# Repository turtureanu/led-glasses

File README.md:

# led-glasses

Simple LED glasses controlled using a XIAO ESP32-S3 microcontroller.

## Credits

XIAO ESP32S3 footprint (XIAO-ESP32S3-SMD.kicad_mod): https://github.com/Seeed-Studio/OPL_Kicad_Library
XIAO ESP32S3 3D model: https://wiki.seeedstudio.com/xiao_esp32s3_getting_started/

Other 3D models sourced from EasyEDA.

## Todo

[-] Add battery switch circuit
[-] switch from 5V to 3V3, because 5V doesn't work with a battery
// breakout pins can be used to make a prototype using a battery
[x] breakout other pins

## BOM

- 62x | SK6812 LEDs: OPSCO Optoelectronics SK6812mini-012
  - https://www.lcsc.com/product-detail/RGB-LEDs-Built-in-IC_OPSCO-Optoelectronics-SK6812mini-012_C2886570.html?s_z=n_SK6812MINI-012
- 1x | 1uF capacitor: Samsung Electro-Mechanics CL31A107MQHNNNE
  - https://www.lcsc.com/product-detail/Multilayer-Ceramic-Capacitors-MLCC-SMD-SMT_Samsung-Electro-Mechanics-CL31A107MQHNNNE_C15008.html
- 3x | 4.7 nF capacitor: FH (Guangdong Fenghua Advanced Tech) 1206B472K102NT
  - https://www.lcsc.com/product-detail/Multilayer-Ceramic-Capacitors-MLCC-SMD-SMT_FH-Guangdong-Fenghua-Advanced-Tech-1206B472K102NT_C9192.html
- 1x | Tactile Switch: XUNPU TS-1088-AR02016
  - https://www.lcsc.com/product-detail/Tactile-Switches_XUNPU-TS-1088-AR02016_C720477.html?s_z=s_Switches%257CTactile%2520Switches

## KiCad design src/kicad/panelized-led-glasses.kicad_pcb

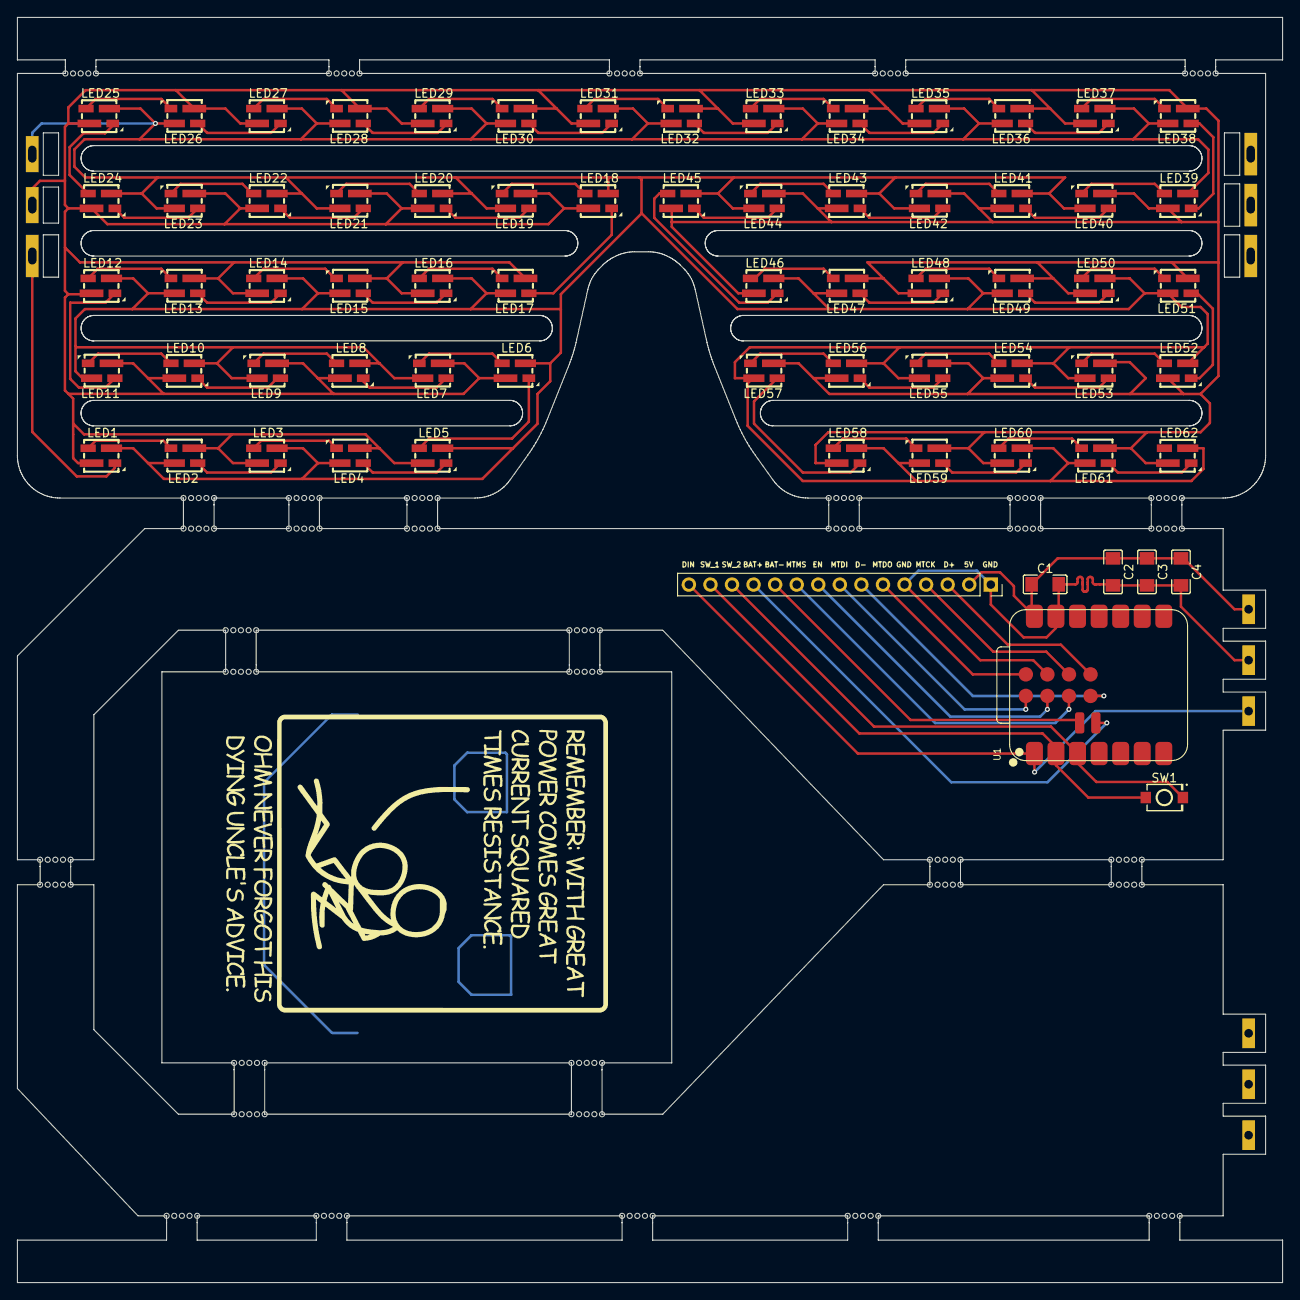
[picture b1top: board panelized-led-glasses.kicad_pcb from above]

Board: 2 copper layers, 149.0 x 149.0 mm, 184 parts (0 on the bottom side), 75 nets.

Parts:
C1: 100uF; Capacitor_C1206_SMD
C2, C3, C4: 4.7nF; Capacitor_C1206_SMD
J1: Conn_01x15_Pin; PinSocket_1x15_P2.54mm_Vertical
KiKit_MB_1_1, KiKit_MB_1_2, KiKit_MB_1_3, KiKit_MB_1_4, KiKit_MB_1_5, KiKit_MB_2_1, KiKit_MB_2_2, KiKit_MB_2_3, KiKit_MB_2_4, KiKit_MB_2_5, KiKit_MB_3_1, KiKit_MB_3_2, KiKit_MB_3_3, KiKit_MB_3_4, KiKit_MB_3_5, KiKit_MB_4_1, KiKit_MB_4_2, KiKit_MB_4_3, KiKit_MB_4_4, KiKit_MB_4_5, KiKit_MB_5_1, KiKit_MB_5_2, KiKit_MB_5_3, KiKit_MB_5_4, KiKit_MB_5_5, KiKit_MB_6_1, KiKit_MB_6_2, KiKit_MB_6_3, KiKit_MB_6_4, KiKit_MB_6_5, KiKit_MB_7_1, KiKit_MB_7_2, KiKit_MB_7_3, KiKit_MB_7_4, KiKit_MB_7_5, KiKit_MB_8_1, KiKit_MB_8_2, KiKit_MB_8_3, KiKit_MB_8_4, KiKit_MB_8_5, KiKit_MB_9_1, KiKit_MB_9_2, KiKit_MB_9_3, KiKit_MB_9_4, KiKit_MB_9_5, KiKit_MB_10_1, KiKit_MB_10_2, KiKit_MB_10_3, KiKit_MB_10_4, KiKit_MB_10_5, KiKit_MB_11_1, KiKit_MB_11_2, KiKit_MB_11_3, KiKit_MB_11_4, KiKit_MB_11_5, KiKit_MB_12_1, KiKit_MB_12_2, KiKit_MB_12_3, KiKit_MB_12_4, KiKit_MB_12_5, KiKit_MB_13_1, KiKit_MB_13_2, KiKit_MB_13_3, KiKit_MB_13_4, KiKit_MB_13_5, KiKit_MB_14_1, KiKit_MB_14_2, KiKit_MB_14_3, KiKit_MB_14_4, KiKit_MB_14_5, KiKit_MB_15_1, KiKit_MB_15_2, KiKit_MB_15_3, KiKit_MB_15_4, KiKit_MB_15_5, KiKit_MB_16_1, KiKit_MB_16_2, KiKit_MB_16_3, KiKit_MB_16_4, KiKit_MB_16_5, KiKit_MB_17_1, KiKit_MB_17_2, KiKit_MB_17_3, KiKit_MB_17_4, KiKit_MB_17_5, KiKit_MB_18_1, KiKit_MB_18_2, KiKit_MB_18_3, KiKit_MB_18_4, KiKit_MB_18_5, KiKit_MB_19_1, KiKit_MB_19_2, KiKit_MB_19_3, KiKit_MB_19_4, KiKit_MB_19_5, KiKit_MB_20_1, KiKit_MB_20_2, KiKit_MB_20_3, KiKit_MB_20_4, KiKit_MB_20_5, KiKit_MB_21_1, KiKit_MB_21_2, KiKit_MB_21_3, KiKit_MB_21_4, KiKit_MB_21_5, KiKit_MB_22_1, KiKit_MB_22_2, KiKit_MB_22_3, KiKit_MB_22_4, KiKit_MB_22_5, KiKit_MB_23_1, KiKit_MB_23_2, KiKit_MB_23_3, KiKit_MB_23_4, KiKit_MB_23_5: NPTH
LED1, LED2, LED3, LED4, LED5, LED6, LED7, LED8, LED9, LED10, LED11, LED12, LED13, LED14, LED15, LED16, LED17, LED18, LED19, LED20, LED21, LED22, LED23, LED24, LED25, LED26, LED27, LED28, LED29, LED30, LED31, LED32, LED33, LED34, LED35, LED36, LED37, LED38, LED39, LED40, LED41, LED42, LED43, LED44, LED45, LED46, LED47, LED48, LED49, LED50, LED51, LED52, LED53, LED54, LED55, LED56, LED57, LED58, LED59, LED60, LED61, LED62: LED-SMD_4P-L3.7-W3.5-P1.75-BR-SK6812MINI
SW1: SW_Push_45deg; SW-SMD_L3.9-W3.0-P4.45
U1: XIAO-ESP32S3-SMD

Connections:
BAT+: J1.12, U1.15 (BAT+)
BAT-: J1.11, U1.16 (BAT-)
D+: J1.3, U1.24 (D+)
D-: J1.7, U1.23 (D-)
EN: J1.9, U1.19 (EN)
LEDS_5V: C1.1, C2.1, C3.1, C4.1, J1.2, LED1.2 (VDD), LED2.2 (VDD), LED3.2 (VDD), LED4.2 (VDD), LED5.2 (VDD), LED6.2 (VDD), LED7.2 (VDD), LED8.2 (VDD), LED9.2 (VDD), LED10.2 (VDD), LED11.2 (VDD), LED12.2 (VDD), LED13.2 (VDD), LED14.2 (VDD), LED15.2 (VDD), LED16.2 (VDD), LED17.2 (VDD), LED18.2 (VDD), LED19.2 (VDD), LED20.2 (VDD), LED21.2 (VDD), LED22.2 (VDD), LED23.2 (VDD), LED24.2 (VDD), LED25.2 (VDD), LED26.2 (VDD), LED27.2 (VDD), LED28.2 (VDD), LED29.2 (VDD), LED30.2 (VDD), LED31.2 (VDD), LED32.2 (VDD), LED33.2 (VDD), LED34.2 (VDD), LED35.2 (VDD), LED36.2 (VDD), LED37.2 (VDD), LED38.2 (VDD), LED39.2 (VDD), LED40.2 (VDD), LED41.2 (VDD), LED42.2 (VDD), LED43.2 (VDD), LED44.2 (VDD), LED45.2 (VDD), LED46.2 (VDD), LED47.2 (VDD), LED48.2 (VDD), LED49.2 (VDD), LED50.2 (VDD), LED51.2 (VDD), LED52.2 (VDD), LED53.2 (VDD), LED54.2 (VDD), LED55.2 (VDD), LED56.2 (VDD), LED57.2 (VDD), LED58.2 (VDD), LED59.2 (VDD), LED60.2 (VDD), LED61.2 (VDD), LED62.2 (VDD), U1.14 (5V)
LEDS_DIN: J1.15, LED1.1 (DIN), U1.1 (D0)
LEDS_GND: C1.2, C2.2, C3.2, C4.2, J1.1, J1.5, LED1.4 (GND), LED2.4 (GND), LED3.4 (GND), LED4.4 (GND), LED5.4 (GND), LED6.4 (GND), LED7.4 (GND), LED8.4 (GND), LED9.4 (GND), LED10.4 (GND), LED11.4 (GND), LED12.4 (GND), LED13.4 (GND), LED14.4 (GND), LED15.4 (GND), LED16.4 (GND), LED17.4 (GND), LED18.4 (GND), LED19.4 (GND), LED20.4 (GND), LED21.4 (GND), LED22.4 (GND), LED23.4 (GND), LED24.4 (GND), LED25.4 (GND), LED26.4 (GND), LED27.4 (GND), LED28.4 (GND), LED29.4 (GND), LED30.4 (GND), LED31.4 (GND), LED32.4 (GND), LED33.4 (GND), LED34.4 (GND), LED35.4 (GND), LED36.4 (GND), LED37.4 (GND), LED38.4 (GND), LED39.4 (GND), LED40.4 (GND), LED41.4 (GND), LED42.4 (GND), LED43.4 (GND), LED44.4 (GND), LED45.4 (GND), LED46.4 (GND), LED47.4 (GND), LED48.4 (GND), LED49.4 (GND), LED50.4 (GND), LED51.4 (GND), LED52.4 (GND), LED53.4 (GND), LED54.4 (GND), LED55.4 (GND), LED56.4 (GND), LED57.4 (GND), LED58.4 (GND), LED59.4 (GND), LED60.4 (GND), LED61.4 (GND), LED62.4 (GND), U1.13 (GND), U1.20 (GND)
MTCK: J1.4, U1.22 (MTCK)
MTDI: J1.8, U1.17 (MTDI)
MTDO: J1.6, U1.18 (MTDO)
MTMS: J1.10, U1.21 (MTMS)
unnamed: LED1.3 (DOUT), LED2.1 (DIN)
unnamed: LED2.3 (DOUT), LED3.1 (DIN)
unnamed: LED3.3 (DOUT), LED4.1 (DIN)
unnamed: LED4.3 (DOUT), LED5.1 (DIN)
unnamed: LED5.3 (DOUT), LED6.1 (DIN)
unnamed: LED6.3 (DOUT), LED7.1 (DIN)
unnamed: LED7.3 (DOUT), LED8.1 (DIN)
unnamed: LED8.3 (DOUT), LED9.1 (DIN)
unnamed: LED9.3 (DOUT), LED10.1 (DIN)
unnamed: LED10.3 (DOUT), LED11.1 (DIN)
unnamed: LED11.3 (DOUT), LED12.1 (DIN)
unnamed: LED12.3 (DOUT), LED13.1 (DIN)
unnamed: LED13.3 (DOUT), LED14.1 (DIN)
unnamed: LED14.3 (DOUT), LED15.1 (DIN)
unnamed: LED15.3 (DOUT), LED16.1 (DIN)
unnamed: LED16.3 (DOUT), LED17.1 (DIN)
unnamed: LED17.3 (DOUT), LED18.1 (DIN)
unnamed: LED18.3 (DOUT), LED19.1 (DIN)
unnamed: LED19.3 (DOUT), LED20.1 (DIN)
unnamed: LED20.3 (DOUT), LED21.1 (DIN)
unnamed: LED21.3 (DOUT), LED22.1 (DIN)
unnamed: LED22.3 (DOUT), LED23.1 (DIN)
unnamed: LED23.3 (DOUT), LED24.1 (DIN)
unnamed: LED24.3 (DOUT), LED25.1 (DIN)
unnamed: LED25.3 (DOUT), LED26.1 (DIN)
unnamed: LED26.3 (DOUT), LED27.1 (DIN)
unnamed: LED27.3 (DOUT), LED28.1 (DIN)
unnamed: LED28.3 (DOUT), LED29.1 (DIN)
unnamed: LED29.3 (DOUT), LED30.1 (DIN)
unnamed: LED30.3 (DOUT), LED31.1 (DIN)
unnamed: LED31.3 (DOUT), LED32.1 (DIN)
unnamed: LED32.3 (DOUT), LED33.1 (DIN)
unnamed: LED33.3 (DOUT), LED34.1 (DIN)
unnamed: LED34.3 (DOUT), LED35.1 (DIN)
unnamed: LED35.3 (DOUT), LED36.1 (DIN)
unnamed: LED36.3 (DOUT), LED37.1 (DIN)
unnamed: LED37.3 (DOUT), LED38.1 (DIN)
unnamed: LED38.3 (DOUT), LED39.1 (DIN)
unnamed: LED39.3 (DOUT), LED40.1 (DIN)
unnamed: LED40.3 (DOUT), LED41.1 (DIN)
unnamed: LED41.3 (DOUT), LED42.1 (DIN)
unnamed: LED42.3 (DOUT), LED43.1 (DIN)
unnamed: LED43.3 (DOUT), LED44.1 (DIN)
unnamed: LED44.3 (DOUT), LED45.1 (DIN)
unnamed: LED45.3 (DOUT), LED46.1 (DIN)
unnamed: LED46.3 (DOUT), LED47.1 (DIN)
unnamed: LED47.3 (DOUT), LED48.1 (DIN)
unnamed: LED48.3 (DOUT), LED49.1 (DIN)
unnamed: LED49.3 (DOUT), LED50.1 (DIN)
unnamed: LED50.3 (DOUT), LED51.1 (DIN)
unnamed: LED51.3 (DOUT), LED52.1 (DIN)
unnamed: LED52.3 (DOUT), LED53.1 (DIN)
unnamed: LED53.3 (DOUT), LED54.1 (DIN)
unnamed: LED54.3 (DOUT), LED55.1 (DIN)
unnamed: LED55.3 (DOUT), LED56.1 (DIN)
unnamed: LED56.3 (DOUT), LED57.1 (DIN)
unnamed: LED57.3 (DOUT), LED58.1 (DIN)
unnamed: LED58.3 (DOUT), LED59.1 (DIN)
unnamed: LED59.3 (DOUT), LED60.1 (DIN)
unnamed: LED60.3 (DOUT), LED61.1 (DIN)
unnamed: LED61.3 (DOUT), LED62.1 (DIN)
SW_1: J1.14, SW1.1, U1.2 (D1)
SW_2: J1.13, SW1.2, U1.3 (D2)

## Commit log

2025-04-12 add: initial files
2025-04-13 feat: final touch ups
